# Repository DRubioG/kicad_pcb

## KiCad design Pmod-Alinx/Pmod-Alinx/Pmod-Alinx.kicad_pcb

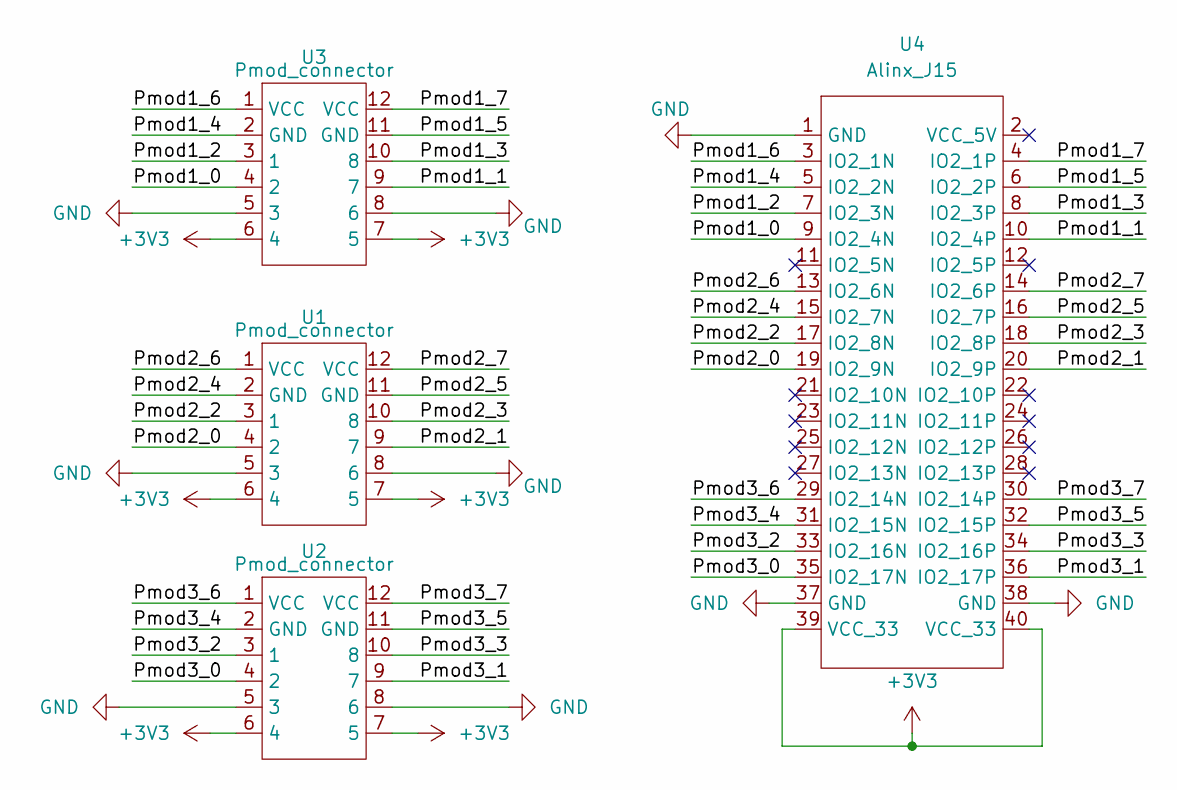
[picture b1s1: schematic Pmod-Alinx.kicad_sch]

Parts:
U1, U2, U3: Pmod_connector; DIP-12_100
U4: Alinx_J15; DIP-40_100

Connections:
+3V3: U1.6 (4), U1.7 (5), U2.6 (4), U2.7 (5), U3.6 (4), U3.7 (5), U4.39 (VCC_33), U4.40 (VCC_33)
/Pmod1_0: U3.4 (2), U4.9 (IO2_4N)
/Pmod1_1: U3.9 (7), U4.10 (IO2_4P)
/Pmod1_2: U3.3 (1), U4.7 (IO2_3N)
/Pmod1_3: U3.10 (8), U4.8 (IO2_3P)
/Pmod1_4: U3.2 (GND), U4.5 (IO2_2N)
/Pmod1_5: U3.11 (GND), U4.6 (IO2_2P)
/Pmod1_6: U3.1 (VCC), U4.3 (IO2_1N)
/Pmod1_7: U3.12 (VCC), U4.4 (IO2_1P)
/Pmod2_0: U1.4 (2), U4.19 (IO2_9N)
/Pmod2_1: U1.9 (7), U4.20 (IO2_9P)
/Pmod2_2: U1.3 (1), U4.17 (IO2_8N)
/Pmod2_3: U1.10 (8), U4.18 (IO2_8P)
/Pmod2_4: U1.2 (GND), U4.15 (IO2_7N)
/Pmod2_5: U1.11 (GND), U4.16 (IO2_7P)
/Pmod2_6: U1.1 (VCC), U4.13 (IO2_6N)
/Pmod2_7: U1.12 (VCC), U4.14 (IO2_6P)
/Pmod3_0: U2.4 (2), U4.35 (IO2_17N)
/Pmod3_1: U2.9 (7), U4.36 (IO2_17P)
/Pmod3_2: U2.3 (1), U4.33 (IO2_16N)
/Pmod3_3: U2.10 (8), U4.34 (IO2_16P)
/Pmod3_4: U2.2 (GND), U4.31 (IO2_15N)
/Pmod3_5: U2.11 (GND), U4.32 (IO2_15P)
/Pmod3_6: U2.1 (VCC), U4.29 (IO2_14N)
/Pmod3_7: U2.12 (VCC), U4.30 (IO2_14P)
GND: U1.5 (3), U1.8 (6), U2.5 (3), U2.8 (6), U3.5 (3), U3.8 (6), U4.1 (GND), U4.37 (GND), U4.38 (GND)

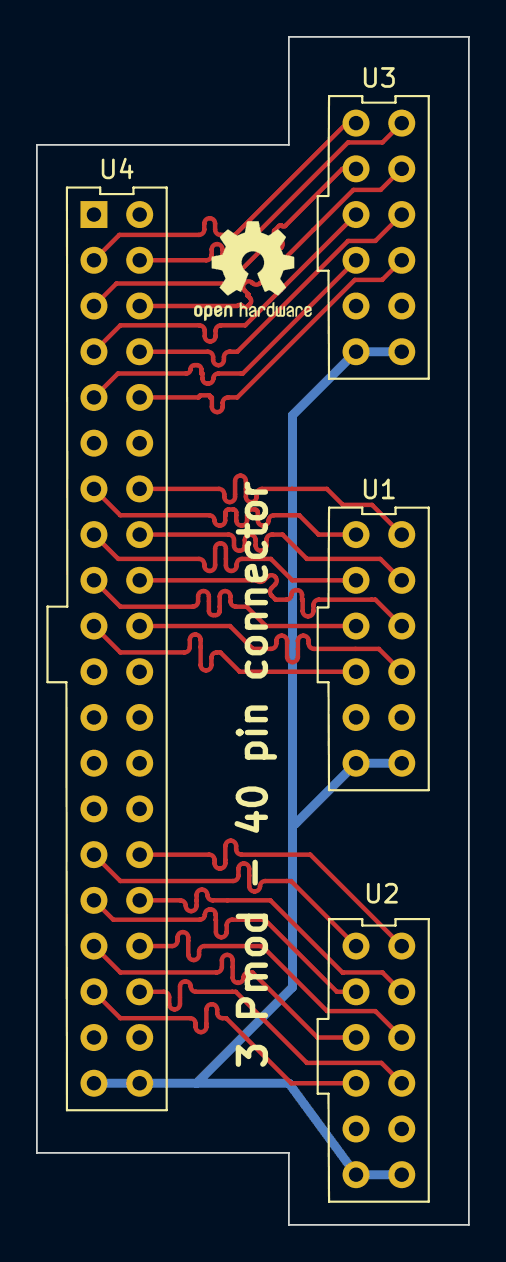
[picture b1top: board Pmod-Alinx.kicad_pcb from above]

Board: 2 copper layers, 24.0 x 66.0 mm, 4 parts (0 on the bottom side), 26 nets.
